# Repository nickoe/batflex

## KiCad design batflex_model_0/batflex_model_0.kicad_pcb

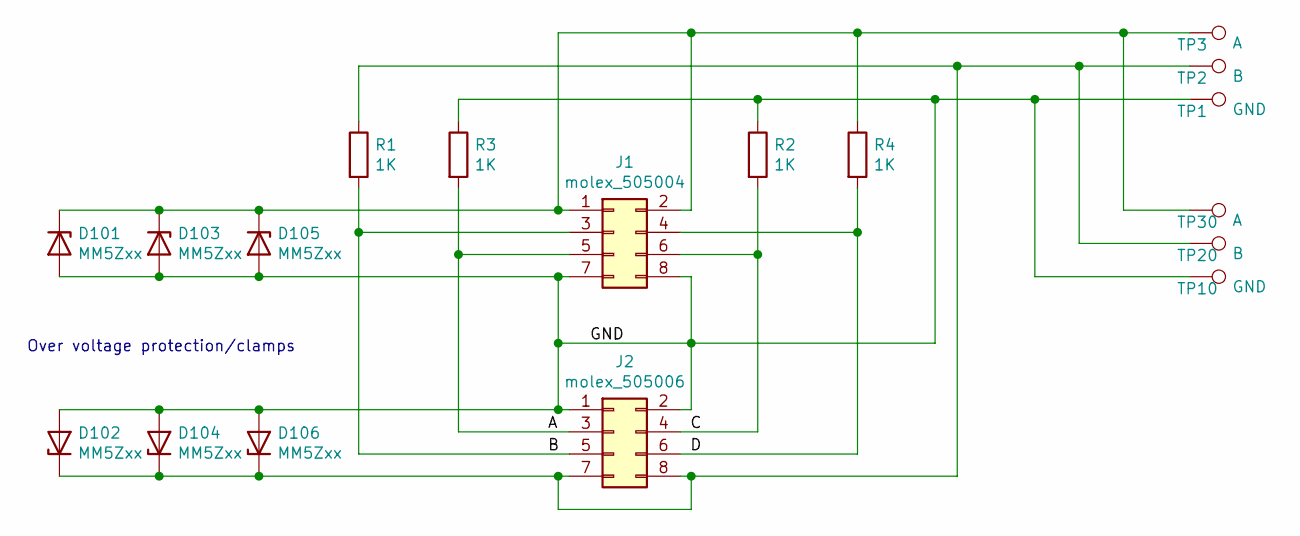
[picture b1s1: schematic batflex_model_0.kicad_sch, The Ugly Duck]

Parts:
D101, D102, D103, D104, D105, D106: MM5Zxx; D_SOD-523; mfg# SZMM5Z4V7ST5G; mouser# 863-SZMM5Z4V7ST5G
J1: molex_505004; molex_5050040812
J2: molex_505006; molex_5050060812
R1, R2, R3, R4: 1K; R_0402_1005Metric
TP1, TP10: GND; wire_pad_2x4mm
TP2, TP20: B; wire_pad_2x4mm
TP3, TP30: A; wire_pad_2x4mm

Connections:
/A: J1.5, J2.3, R3.2
/B: J1.3, J2.5, R1.2
/C: J1.6, J2.4, R2.2
/D: J1.4, J2.6, R4.2
/GND: D101.2 (A), D102.2 (A), D103.2 (A), D104.2 (A), D105.2 (A), D106.2 (A), J1.7, J1.8, J2.1, J2.2, R2.1, R3.1, TP1.1, TP10.1
unnamed: D101.1 (K), D103.1 (K), D105.1 (K), J1.1, J1.2, R4.1, TP3.1, TP30.1
unnamed: D102.1 (K), D104.1 (K), D106.1 (K), J2.7, J2.8, R1.1, TP2.1, TP20.1

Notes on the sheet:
Over voltage protection/clamps

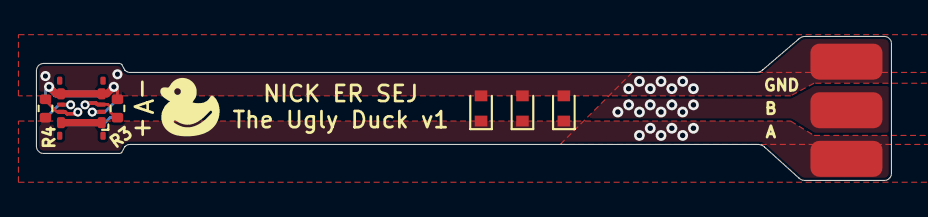
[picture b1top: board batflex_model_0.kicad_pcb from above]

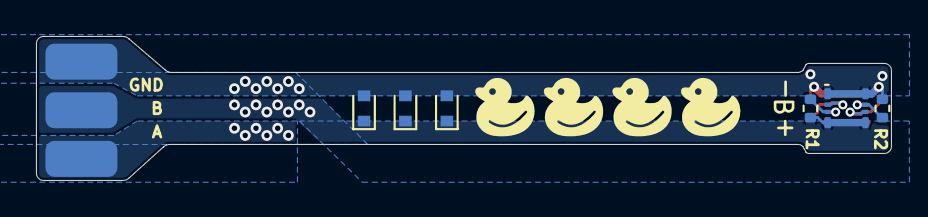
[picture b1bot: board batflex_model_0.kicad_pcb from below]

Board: 2 copper layers, 47.5 x 8.0 mm, 18 parts (9 on the bottom side), 7 nets.

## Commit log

2020-11-03 Add 3d model for 505004
2020-11-03 Add footprint for 505004
2020-11-03 Update schematic to prepare for ugly duckling
2020-11-03 Add footprints to resistors...
2020-11-04 Almost final design, TODO, fix duck, add clamps diodes
2020-11-04 First iteration of layout wiht 0402 resistors
2020-11-04 Add protection and fix duck
2020-11-04 Add random version string and date
2020-11-04 Add mechanical pads to female connector
2020-11-04 Minor tweaks
2020-11-06 Final PCB for batflex model 0 aka the ugly duck
